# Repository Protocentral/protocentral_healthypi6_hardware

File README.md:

<div align="center">

<picture>
  <source media="(prefers-color-scheme: dark)" srcset="docs/images/healthypi6-logo-dark.png">
  
</picture>

</div>

# HealthyPi 6 — Hardware

Open hardware design files for HealthyPi 6, a standalone vital-signs monitor with a
modular expansion bus.

The device is built around a tri-core architecture — an STM32H757BI (Cortex-M7 +
Cortex-M4) with an ESP32-C6 for wireless — with a 4" capacitive touchscreen, an isolated
supply, an isolated USB port, and two HealthyLink expansion slots that accept new sensing
front-ends without a board respin.

This repository holds the KiCad schematics and PCB layouts, the HealthyLink interface
definition, the enclosure CAD, and the CE/UKCA declarations of conformity.

## Links

| | |
|---|---|
| Product page | https://www.crowdsupply.com/protocentral/healthypi-6 |
| Firmware (Zephyr) | https://github.com/Protocentral/healthypi-6-fw |
| HealthyPi Studio | https://github.com/Protocentral/healthypi_studio |

## Boards

Design files are published as each board is finalised.

| Board | Revision | Role |
|---|---|---|
| [`healthypi_6_main_v5`](hardware/healthypi_6_main_v5/) | **v5** | STM32H757BI main board — AFEs, power, wireless, both HealthyLink slots |
| [`healthypi_6_display_v7`](hardware/healthypi_6_display_v7/) | **v7** | Display interface board — MIPI-DSI and touch to the panel, backlight driver |
| [`healthylink_compute_v5`](hardware/healthylink_compute_v5/) | **v5** | HealthyLink compute / NPU module — STM32N657, camera, storage |
| [`healthylink_gpio_v2`](hardware/healthylink_gpio_v2/) | **v2** | HealthyLink GPIO breakout — the minimal module example |

## Specifications

Cross-checked against the v5 schematic in this repository.

- **Application processor:** STM32H757BI (LQFP208) — Arm Cortex-M7 @ 400 MHz +
  Cortex-M4 @ 200 MHz
- **Wireless:** ESP32-C6-MINI-1 (Wi-Fi 6 / BLE / 802.15.4), UART and SPI to the host MCU,
  plus its own USB-C for direct flashing
- **Display:** 4" 480×800 capacitive touchscreen — 2-lane MIPI-DSI, touch on I²C,
  TPS61158 backlight boost on the display board
- **Biosignal front-ends:** TI ADS1294R (ECG + thoracic respiration), TI AFE4400 (PPG),
  Bosch BMI323 (motion)
- **Expansion:** 2 × HealthyLink slots, 2 × Hirose DF9-31P-1V per slot (62 pins/slot),
  per-slot NCP380 current-limited load switch with fault reporting
- **Power:** isolated 10 W supply (Traco THM 10-0511); TI BQ24074 linear battery charger,
  Maxim MAX17048 fuel gauge, TPS62A02 system buck
- **Memory and storage:** 32 MB SDRAM (Winbond W9825G6KH), 64 MB QSPI NOR
  (Winbond W25Q512JV), microSD
- **Host interface:** USB-C, USB 2.0 full-speed, galvanically isolated through a
  TI ISOUSB111
- **Main board:** 120 × 70 mm, 6-layer

## HealthyLink expansion bus

HealthyLink is the modular expansion system for HealthyPi 6. Each slot presents 62 pins
across two Hirose DF9-31 board-to-board connectors, carrying two SPI buses, I²C, a UART,
six analog inputs, CAN, per-slot interrupt and reset, and a switched 3V3 module rail. The
main board has two slots (A and B).

Modules are **not hot-swappable** — install them with the device powered off.

The full pin assignment and electrical definition is in
[`docs/HEALTHYLINK.md`](docs/HEALTHYLINK.md). The KiCad symbol for the connector is
[`hardware/healthylink_df9_connector.kicad_sym`](hardware/healthylink_df9_connector.kicad_sym) —
use it as the starting point for your own module.

## Enclosure

[`enclosure/`](enclosure/) holds the CAD for the case, in three forms: the editable
Fusion archive, a neutral STEP export per part, and a print-ready STL per part.

| Part | Size |
|---|---|
| `top` | 125 × 75 × 23 mm |
| `bottom` | 125 × 75 × 14 mm |
| `back-cover-with-slots` | 125 × 75 × 3 mm |
| `back-cover-no-slots` | 125 × 75 × 7.5 mm |
| `battery-holder` | 53 × 35 × 14 mm |
| `push-switch` | 8 × 5 × 4 mm |
| `slide-switch` | 7 × 13 × 5 mm |

Every part appears under the same name in both
[`enclosure/step/`](enclosure/step/) and [`enclosure/stl/`](enclosure/stl/). The Fusion
source is [`enclosure/source/healthypi6-enclosure-v5.f3z`](enclosure/source/); open it if
you want to change the geometry rather than print it as-is. The enclosure is drawn around
the 120 × 70 mm main board, so any board modification that moves a connector or a mounting
hole needs a matching change here.

## Repository layout

| Path | Contents |
|---|---|
| [`hardware/`](hardware/) | One folder per board: KiCad project (schematic + PCB) and exported schematic PDF |
| [`docs/`](docs/) | HealthyLink interface definition and images |
| [`enclosure/`](enclosure/) | Enclosure CAD — Fusion source, STEP and STL per part |
| [`compliance/`](compliance/) | CE and UKCA declarations of conformity, safety insert |

## Working from these files

- For firmware, start at the firmware repository. This repo is the electrical reference:
  pin assignments, AFE wiring, connector pinouts.
- To build a HealthyLink module, read [`docs/HEALTHYLINK.md`](docs/HEALTHYLINK.md) and
  copy [`healthylink_gpio_v2`](hardware/healthylink_gpio_v2/), which is the minimal
  working example.
- To respin a board: both projects are saved in **KiCad 10** format and will not open in
  earlier versions. Footprints are embedded in the board files and symbols are cached in
  the schematics, so the projects open standalone. A handful of 3D models resolve through
  an internal `${PROTOCENTRAL}` path and will show as missing in the 3D viewer; this
  affects rendering only, never the netlist or the layout.

## Important notice

This device is intended for **research, education, and evaluation use only**. It is **not**
a medical diagnostic instrument, and it is not FDA-approved or otherwise cleared for
clinical or consumer diagnostic use. The CE and UKCA declarations in
[`compliance/`](compliance/) cover EMC and electrical safety for the device as an
electronic product — they are not medical device certifications.

Do not use HealthyPi 6 to make medical decisions.

## License

The hardware design files in this repository are licensed under the **CERN Open Hardware
Licence Version 2 – Permissive (CERN-OHL-P v2)**. See [LICENSE](LICENSE).

Firmware and software for HealthyPi 6 are licensed separately under the MIT License in
their own repositories.

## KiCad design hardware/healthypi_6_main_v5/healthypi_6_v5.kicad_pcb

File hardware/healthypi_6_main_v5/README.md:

# HealthyPi 6 Main Board

| | |
|---|---|
| Revision | **v5** |
| Role | STM32H757BI host, AFEs, power, wireless, 2 × HealthyLink slots |
| Board | 120 × 70 mm, 6-layer |
| KiCad | 10 |
| Schematic PDF | [`healthypi6-main-v5-schematic.pdf`](healthypi6-main-v5-schematic.pdf) |

## Files

| File | Contents |
|---|---|
| `healthypi_6_v5.kicad_pro` / `.kicad_sch` / `.kicad_pcb` | KiCad project for this revision |
| `healthypi6-main-v5-schematic.pdf` | Exported schematic — the human-readable reference |

## Schematic sheets

| Sheet | File | Contents |
|---|---|---|
| MCU | `mcu.kicad_sch` | STM32H757BI, clocks, SWD, buttons, buzzer |
| ECG Frontend | `ecg_afe.kicad_sch` | TI ADS1294R, ECG input protection |
| PPG Frontend | `ppg_sensor.kicad_sch` | TI AFE4400, Bosch BMI323, DE9 patient connector |
| Memory | `memory.kicad_sch` | SDRAM, QSPI NOR, microSD |
| USB | `io.kicad_sch` | USB-C, ISOUSB111 isolator, isolated 10 W supply |
| Power | `power.kicad_sch` | Battery charger, fuel gauge, system rails |
| Power 2 | `power2.kicad_sch` | Per-slot HealthyLink load switches |
| Wireless | `wireless.kicad_sch` | ESP32-C6-MINI-1 and its USB-C |
| connectors | `connectors.kicad_sch` | Display FFC, front-panel and auxiliary connectors |
| healthylink | `healthylink.kicad_sch` | Both HealthyLink slots — see [`docs/HEALTHYLINK.md`](../../docs/HEALTHYLINK.md) |

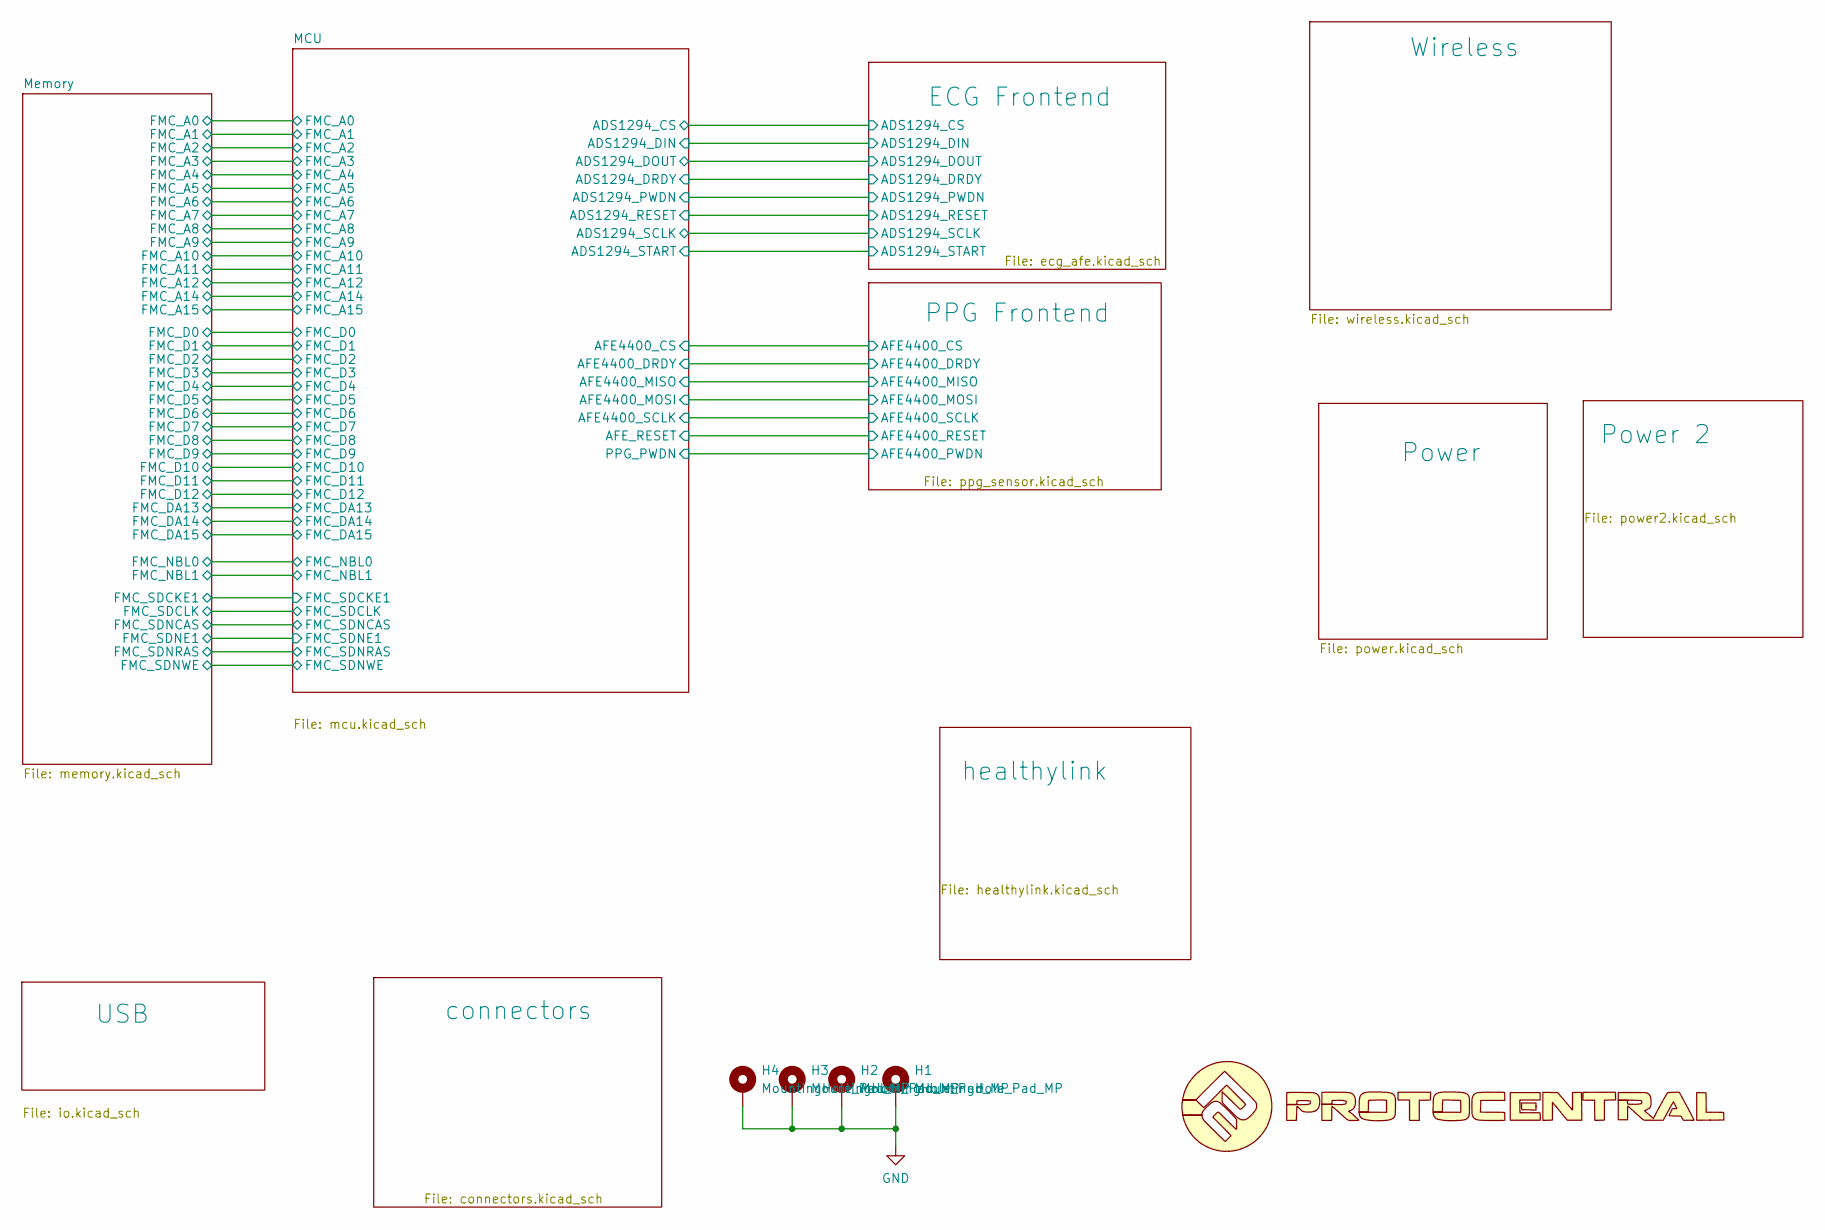
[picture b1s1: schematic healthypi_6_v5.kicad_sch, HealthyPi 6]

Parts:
H1, H2, H3, H4: MountingHole_Pad_MP; MountingHole_3.2mm_M3_DIN965_Pad_TopBottom
U4: LOGO

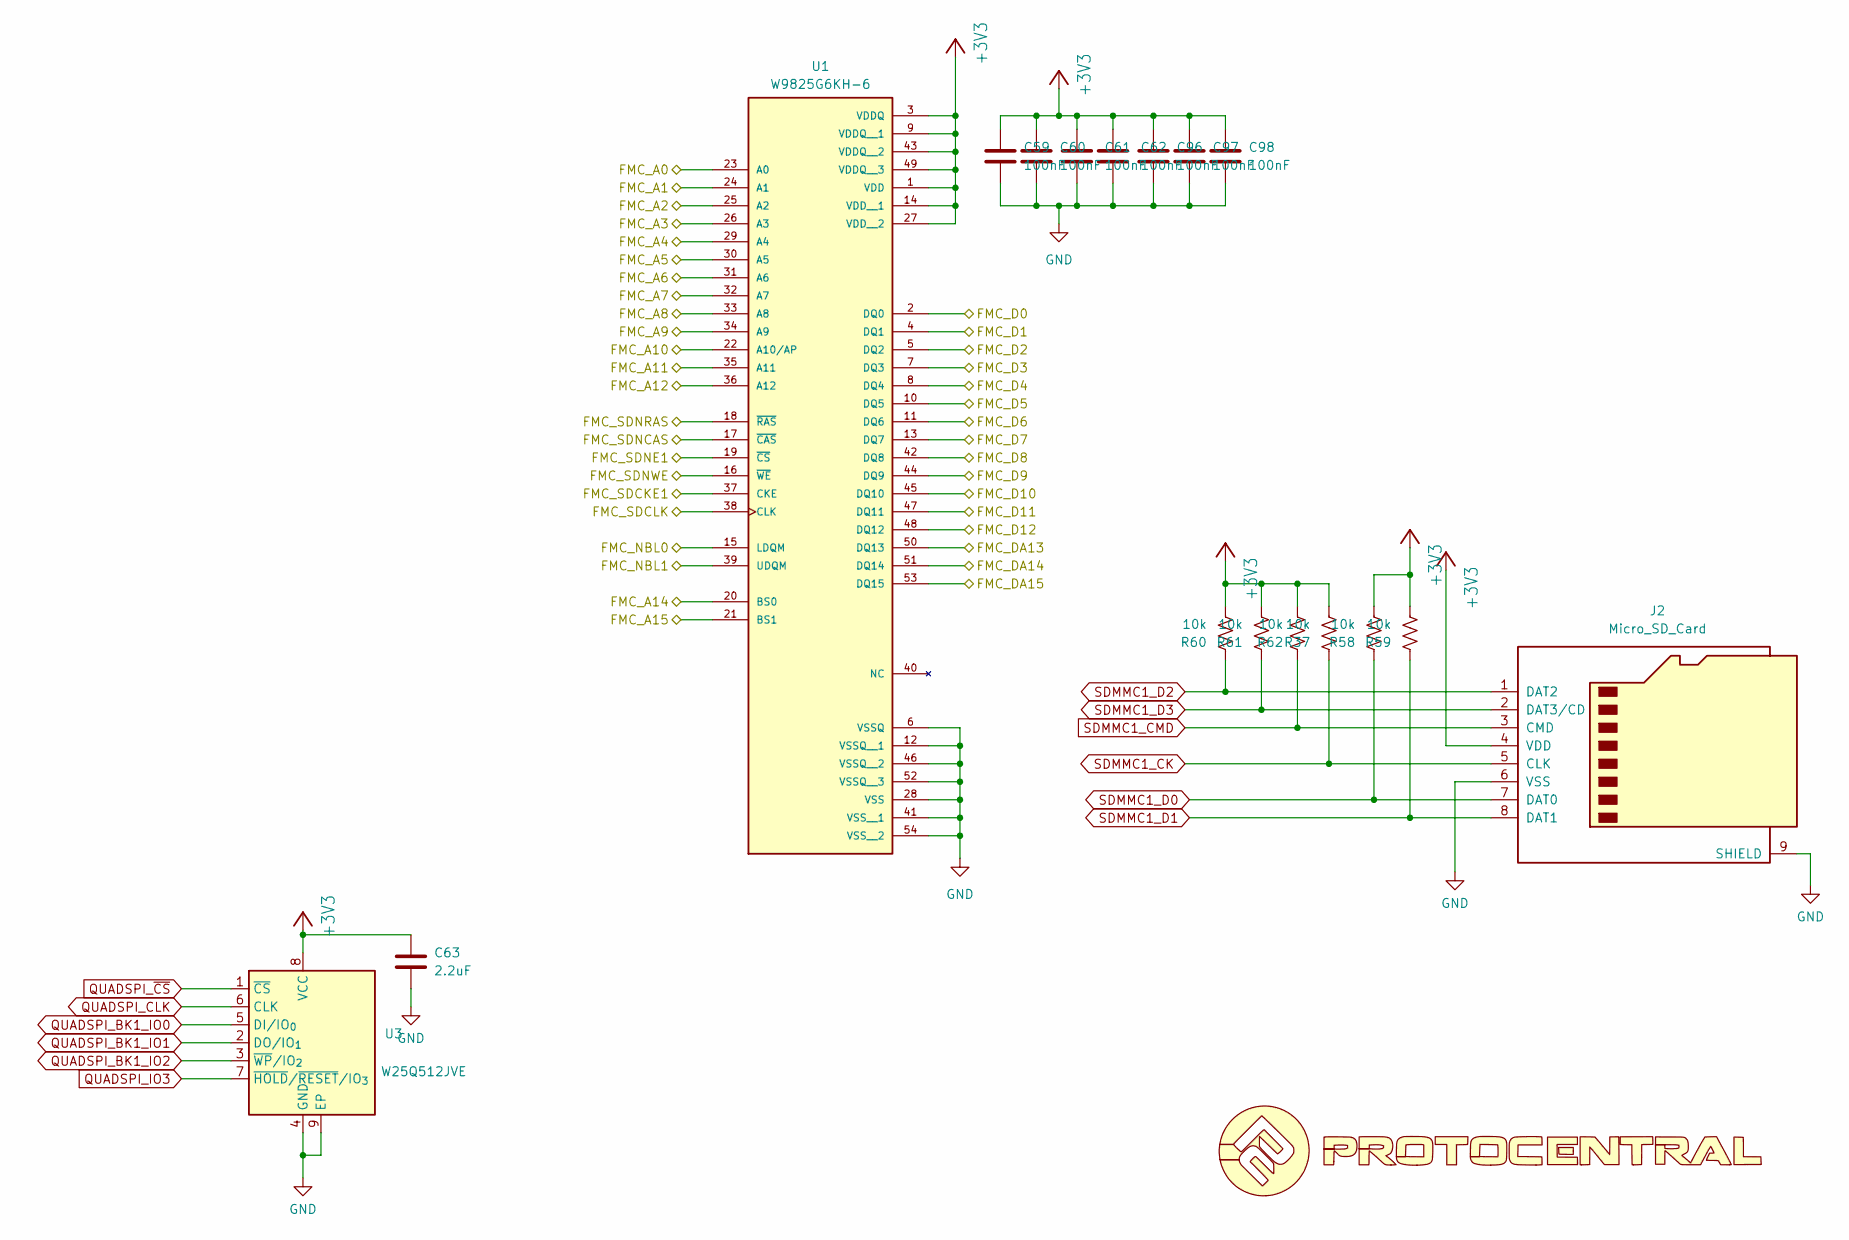
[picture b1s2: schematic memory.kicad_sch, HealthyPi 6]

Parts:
C59, C60, C61, C62, C96, C97, C98: 100nF; C_0402_1005Metric
C63: 2.2uF; C_0402_1005Metric
J2: Micro_SD_Card; GCT_MEM2052-00-195-00-A_REVA
R37, R58, R59, R60, R61, R62: 10k; R_0402_1005Metric
U1: W9825G6KH-6; SOP80P1176X120-54N; PARTREV A05
U3: W25Q512JVE; WSON-8-1EP_8x6mm_P1.27mm_EP3.4x4.3mm
U16: LOGO

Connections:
+3V3: C59.2, C60.2, C61.2, C62.2, C63.2, C96.2, C97.2, C98.2, J2.4 (VDD), R37.2, R58.2, R59.2, R60.2, R61.2, R62.2, U1.1 (VDD), U1.3 (VDDQ), U1.9 (VDDQ__1), U1.14 (VDD__1), U1.27 (VDD__2), U1.43 (VDDQ__2), U1.49 (VDDQ__3), U3.8 (VCC); also elsewhere on the board
/MCU/FMC_A0: U1.23 (A0); also elsewhere on the board
/MCU/FMC_A1: U1.24 (A1); also elsewhere on the board
/MCU/FMC_A2: U1.25 (A2); also elsewhere on the board
/MCU/FMC_A3: U1.26 (A3); also elsewhere on the board
/MCU/FMC_A4: U1.29 (A4); also elsewhere on the board
/MCU/FMC_A5: U1.30 (A5); also elsewhere on the board
/MCU/FMC_A6: U1.31 (A6); also elsewhere on the board
/MCU/FMC_A7: U1.32 (A7); also elsewhere on the board
/MCU/FMC_A8: U1.33 (A8); also elsewhere on the board
/MCU/FMC_A9: U1.34 (A9); also elsewhere on the board
/MCU/FMC_A10: U1.22 (A10/AP); also elsewhere on the board
/MCU/FMC_A11: U1.35 (A11); also elsewhere on the board
/MCU/FMC_A12: U1.36 (A12); also elsewhere on the board
/MCU/FMC_A14: U1.20 (BS0); also elsewhere on the board
/MCU/FMC_A15: U1.21 (BS1); also elsewhere on the board
/MCU/FMC_D0: U1.2 (DQ0); also elsewhere on the board
/MCU/FMC_D1: U1.4 (DQ1); also elsewhere on the board
/MCU/FMC_D2: U1.5 (DQ2); also elsewhere on the board
/MCU/FMC_D3: U1.7 (DQ3); also elsewhere on the board
/MCU/FMC_D4: U1.8 (DQ4); also elsewhere on the board
/MCU/FMC_D5: U1.10 (DQ5); also elsewhere on the board
/MCU/FMC_D6: U1.11 (DQ6); also elsewhere on the board
/MCU/FMC_D7: U1.13 (DQ7); also elsewhere on the board
/MCU/FMC_D8: U1.42 (DQ8); also elsewhere on the board
/MCU/FMC_D9: U1.44 (DQ9); also elsewhere on the board
/MCU/FMC_D10: U1.45 (DQ10); also elsewhere on the board
/MCU/FMC_D11: U1.47 (DQ11); also elsewhere on the board
/MCU/FMC_D12: U1.48 (DQ12); also elsewhere on the board
/MCU/FMC_DA13: U1.50 (DQ13); also elsewhere on the board
/MCU/FMC_DA14: U1.51 (DQ14); also elsewhere on the board
/MCU/FMC_DA15: U1.53 (DQ15); also elsewhere on the board
/MCU/FMC_NBL0: U1.15 (LDQM); also elsewhere on the board
/MCU/FMC_NBL1: U1.39 (UDQM); also elsewhere on the board
/MCU/FMC_SDCKE1: U1.37 (CKE); also elsewhere on the board
/MCU/FMC_SDCLK: U1.38 (CLK); also elsewhere on the board
/MCU/FMC_SDNCAS: U1.17 (~CAS); also elsewhere on the board
/MCU/FMC_SDNE1: U1.19 (~CS); also elsewhere on the board
/MCU/FMC_SDNRAS: U1.18 (~RAS); also elsewhere on the board
/MCU/FMC_SDNWE: U1.16 (~WE); also elsewhere on the board
GND: C59.1, C60.1, C61.1, C62.1, C63.1, C96.1, C97.1, C98.1, J2.6 (VSS), J2.9 (SHIELD), U1.6 (VSSQ), U1.12 (VSSQ__1), U1.28 (VSS), U1.41 (VSS__1), U1.46 (VSSQ__2), U1.52 (VSSQ__3), U1.54 (VSS__2), U3.4 (GND), U3.9 (EP); also elsewhere on the board
QUADSPI_BK1_IO0: U3.5 (DI/IO_{0}); also elsewhere on the board
QUADSPI_BK1_IO1: U3.2 (DO/IO_{1}); also elsewhere on the board
QUADSPI_BK1_IO2: U3.3 (~WP/IO_{2}); also elsewhere on the board
QUADSPI_CLK: U3.6 (CLK); also elsewhere on the board
QUADSPI_IO3: U3.7 (~HOLD/~RESET/IO_{3}); also elsewhere on the board
QUADSPI_~CS: U3.1 (~CS); also elsewhere on the board
SDMMC1_CK: J2.5 (CLK), R37.1; also elsewhere on the board
SDMMC1_CMD: J2.3 (CMD), R62.1; also elsewhere on the board
SDMMC1_D0: J2.7 (DAT0), R58.1; also elsewhere on the board
SDMMC1_D1: J2.8 (DAT1), R59.1; also elsewhere on the board
SDMMC1_D2: J2.1 (DAT2), R60.1; also elsewhere on the board
SDMMC1_D3: J2.2 (DAT3/CD), R61.1; also elsewhere on the board

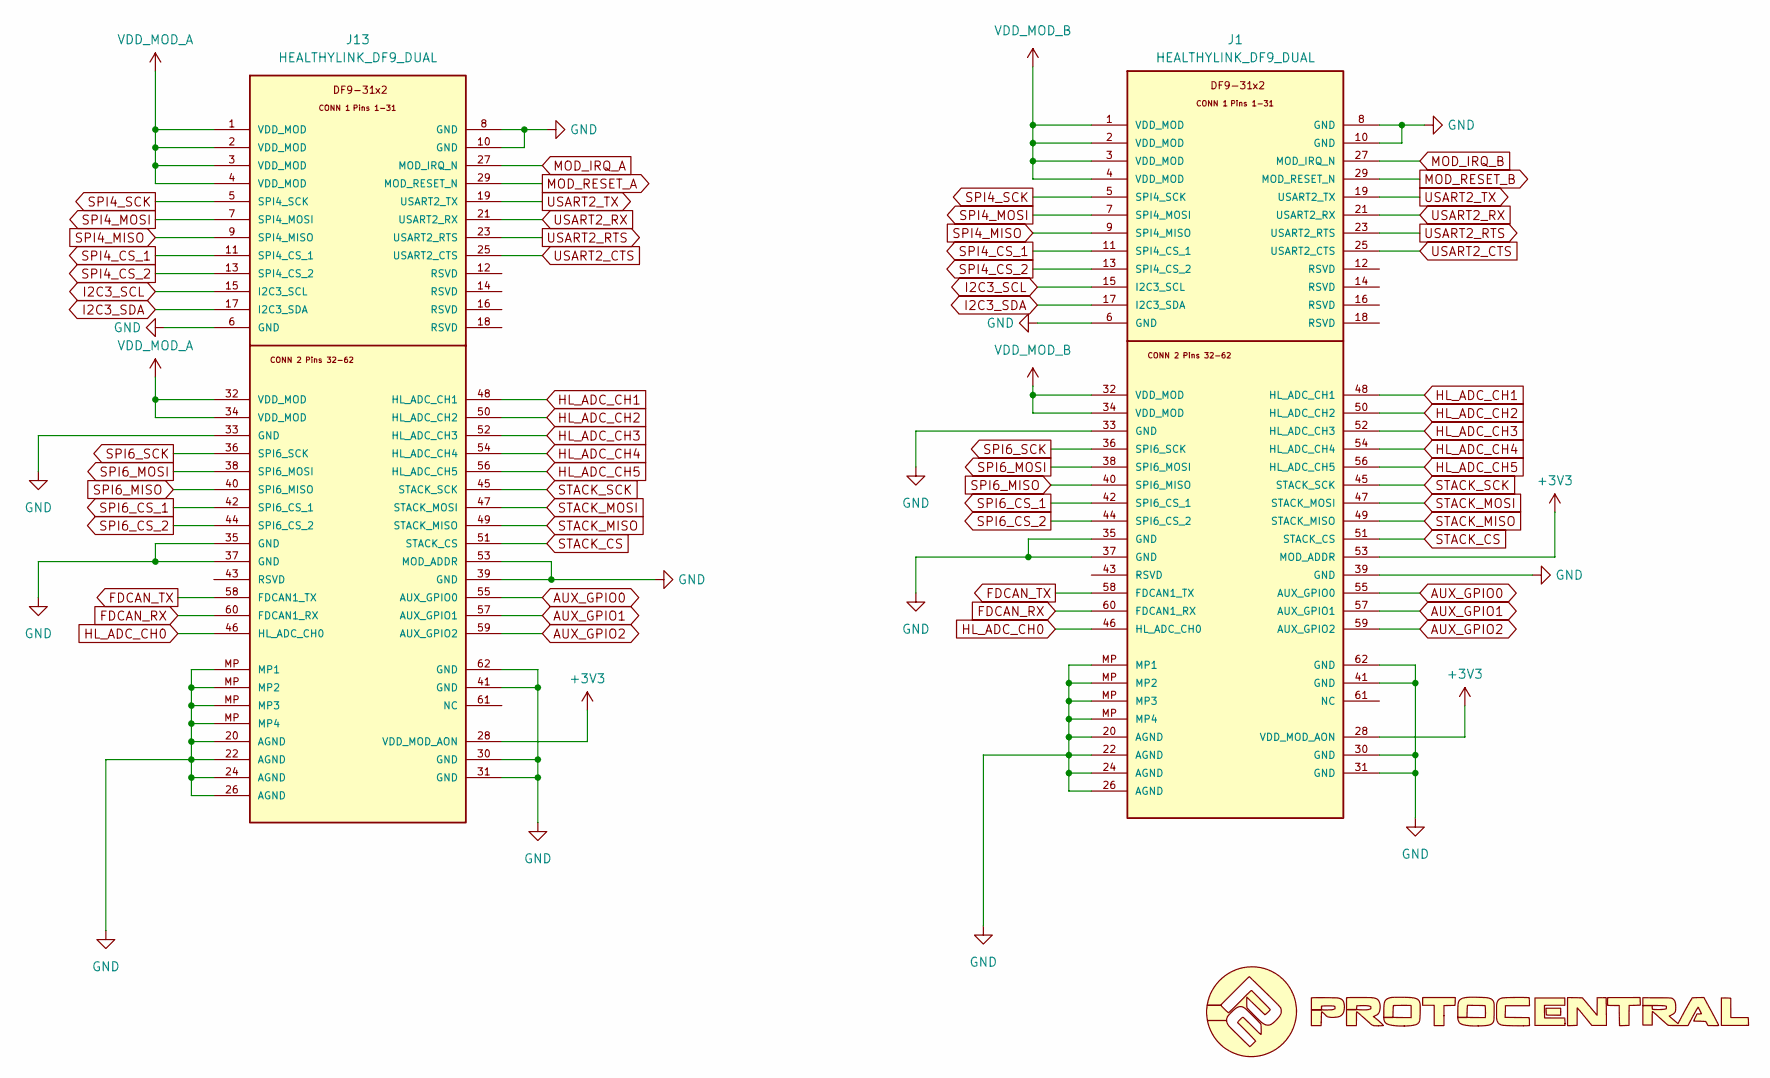
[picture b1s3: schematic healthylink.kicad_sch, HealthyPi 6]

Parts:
J1, J13: HEALTHYLINK_DF9_DUAL; healthylink_df9_module_slot
U23: LOGO

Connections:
+3V3: J1.28 (VDD_MOD_AON), J1.53 (MOD_ADDR), J13.28 (VDD_MOD_AON); also elsewhere on the board
AUX_GPIO0: J1.55 (AUX_GPIO0), J13.55 (AUX_GPIO0); also elsewhere on the board
AUX_GPIO1: J1.57 (AUX_GPIO1), J13.57 (AUX_GPIO1); also elsewhere on the board
AUX_GPIO2: J1.59 (AUX_GPIO2), J13.59 (AUX_GPIO2); also elsewhere on the board
FDCAN_RX: J1.60 (FDCAN1_RX), J13.60 (FDCAN1_RX); also elsewhere on the board
FDCAN_TX: J1.58 (FDCAN1_TX), J13.58 (FDCAN1_TX); also elsewhere on the board
GND: J1.6 (GND), J1.8 (GND), J1.10 (GND), J1.20 (AGND), J1.22 (AGND), J1.24 (AGND), J1.26 (AGND), J1.30 (GND), J1.31 (GND), J1.33 (GND), J1.35 (GND), J1.37 (GND), J1.39 (GND), J1.41 (GND), J1.62 (GND), J1.MP (MP4), J13.6 (GND), J13.8 (GND), J13.10 (GND), J13.20 (AGND), J13.22 (AGND), J13.24 (AGND), J13.26 (AGND), J13.30 (GND), J13.31 (GND), J13.33 (GND), J13.35 (GND), J13.37 (GND), J13.39 (GND), J13.41 (GND), J13.53 (MOD_ADDR), J13.62 (GND), J13.MP (MP1); also elsewhere on the board
HL_ADC_CH0: J1.46 (HL_ADC_CH0), J13.46 (HL_ADC_CH0); also elsewhere on the board
HL_ADC_CH1: J1.48 (HL_ADC_CH1), J13.48 (HL_ADC_CH1); also elsewhere on the board
HL_ADC_CH2: J1.50 (HL_ADC_CH2), J13.50 (HL_ADC_CH2); also elsewhere on the board
HL_ADC_CH3: J1.52 (HL_ADC_CH3), J13.52 (HL_ADC_CH3); also elsewhere on the board
HL_ADC_CH4: J1.54 (HL_ADC_CH4), J13.54 (HL_ADC_CH4); also elsewhere on the board
HL_ADC_CH5: J1.56 (HL_ADC_CH5), J13.56 (HL_ADC_CH5); also elsewhere on the board
I2C3_SCL: J1.15 (I2C3_SCL), J13.15 (I2C3_SCL); also elsewhere on the board
I2C3_SDA: J1.17 (I2C3_SDA), J13.17 (I2C3_SDA); also elsewhere on the board
MOD_IRQ_A: J13.27 (MOD_IRQ_N); also elsewhere on the board
MOD_IRQ_B: J1.27 (MOD_IRQ_N); also elsewhere on the board
MOD_RESET_A: J13.29 (MOD_RESET_N); also elsewhere on the board
MOD_RESET_B: J1.29 (MOD_RESET_N); also elsewhere on the board
SPI4_CS_1: J1.11 (SPI4_CS_1), J13.11 (SPI4_CS_1); also elsewhere on the board
SPI4_CS_2: J1.13 (SPI4_CS_2), J13.13 (SPI4_CS_2); also elsewhere on the board
SPI4_MISO: J1.9 (SPI4_MISO), J13.9 (SPI4_MISO); also elsewhere on the board
SPI4_MOSI: J1.7 (SPI4_MOSI), J13.7 (SPI4_MOSI); also elsewhere on the board
SPI4_SCK: J1.5 (SPI4_SCK), J13.5 (SPI4_SCK); also elsewhere on the board
SPI6_CS_1: J1.42 (SPI6_CS_1), J13.42 (SPI6_CS_1); also elsewhere on the board
SPI6_CS_2: J1.44 (SPI6_CS_2), J13.44 (SPI6_CS_2); also elsewhere on the board
SPI6_MISO: J1.40 (SPI6_MISO), J13.40 (SPI6_MISO); also elsewhere on the board
SPI6_MOSI: J1.38 (SPI6_MOSI), J13.38 (SPI6_MOSI); also elsewhere on the board
SPI6_SCK: J1.36 (SPI6_SCK), J13.36 (SPI6_SCK); also elsewhere on the board
STACK_CS: J1.51 (STACK_CS), J13.51 (STACK_CS)
STACK_MISO: J1.49 (STACK_MISO), J13.49 (STACK_MISO)
STACK_MOSI: J1.47 (STACK_MOSI), J13.47 (STACK_MOSI)
STACK_SCK: J1.45 (STACK_SCK), J13.45 (STACK_SCK)
USART2_CTS: J1.25 (USART2_CTS), J13.25 (USART2_CTS); also elsewhere on the board
USART2_RTS: J1.23 (USART2_RTS), J13.23 (USART2_RTS); also elsewhere on the board
USART2_RX: J1.21 (USART2_RX), J13.21 (USART2_RX); also elsewhere on the board
USART2_TX: J1.19 (USART2_TX), J13.19 (USART2_TX); also elsewhere on the board
VDD_MOD_A: J13.1 (VDD_MOD), J13.2 (VDD_MOD), J13.3 (VDD_MOD), J13.4 (VDD_MOD), J13.32 (VDD_MOD), J13.34 (VDD_MOD); also elsewhere on the board
VDD_MOD_B: J1.1 (VDD_MOD), J1.2 (VDD_MOD), J1.3 (VDD_MOD), J1.4 (VDD_MOD), J1.32 (VDD_MOD), J1.34 (VDD_MOD); also elsewhere on the board

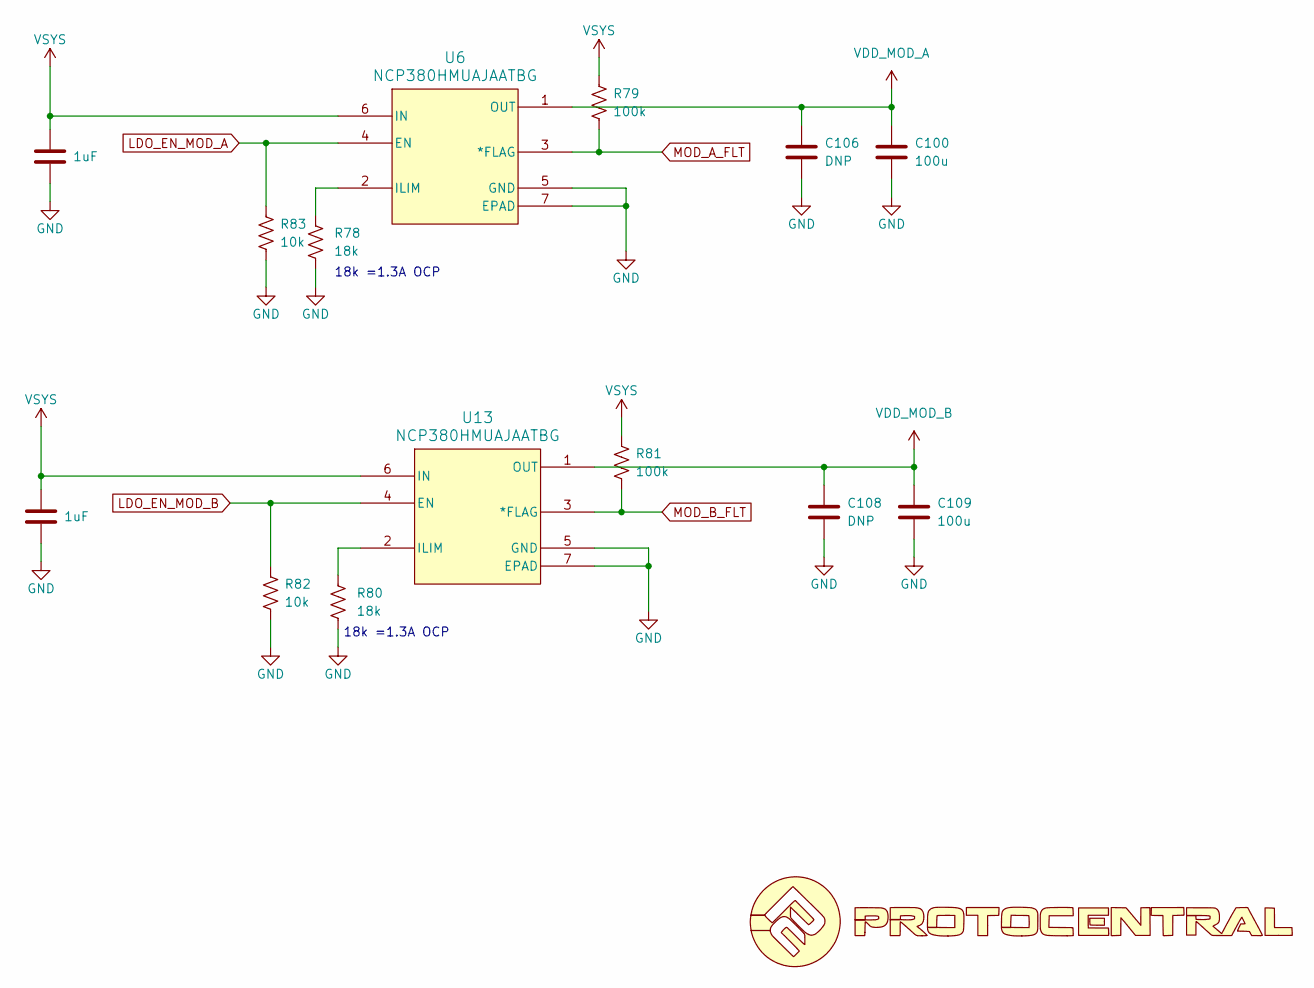
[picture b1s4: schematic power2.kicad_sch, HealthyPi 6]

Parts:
C75, C107: 1uF; C_0402_1005Metric; Voltage 10V; Tolerance 20%
C100, C109: 100u; C_1206_3216Metric
C106, C108: DNP; C_0805_2012Metric
R78, R80: 18k; R_0402_1005Metric
R79, R81: 100k; R_0402_1005Metric
R82, R83: 10k; R_0402_1005Metric
U6, U13: NCP380HMUAJAATBG; UDFN6_2X2_ONS
U24: LOGO

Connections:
GND: C75.2, C100.2, C106.2, C107.2, C108.2, C109.2, R78.1, R80.1, R82.1, R83.1, U6.5 (GND), U6.7 (EPAD), U13.5 (GND), U13.7 (EPAD); also elsewhere on the board
LDO_EN_MOD_A: R83.2, U6.4 (EN); also elsewhere on the board
LDO_EN_MOD_B: R82.2, U13.4 (EN); also elsewhere on the board
MOD_A_FLT: R79.1, U6.3 (*FLAG); also elsewhere on the board
MOD_B_FLT: R81.1, U13.3 (*FLAG); also elsewhere on the board
unnamed: R78.2, U6.2 (ILIM)
unnamed: R80.2, U13.2 (ILIM)
VDD_MOD_A: C100.1, C106.1, U6.1 (OUT); also elsewhere on the board
VDD_MOD_B: C108.1, C109.1, U13.1 (OUT); also elsewhere on the board
VSYS: C75.1, C107.1, R79.2, R81.2, U6.6 (IN), U13.6 (IN); also elsewhere on the board

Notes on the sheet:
18k =1.3A OCP

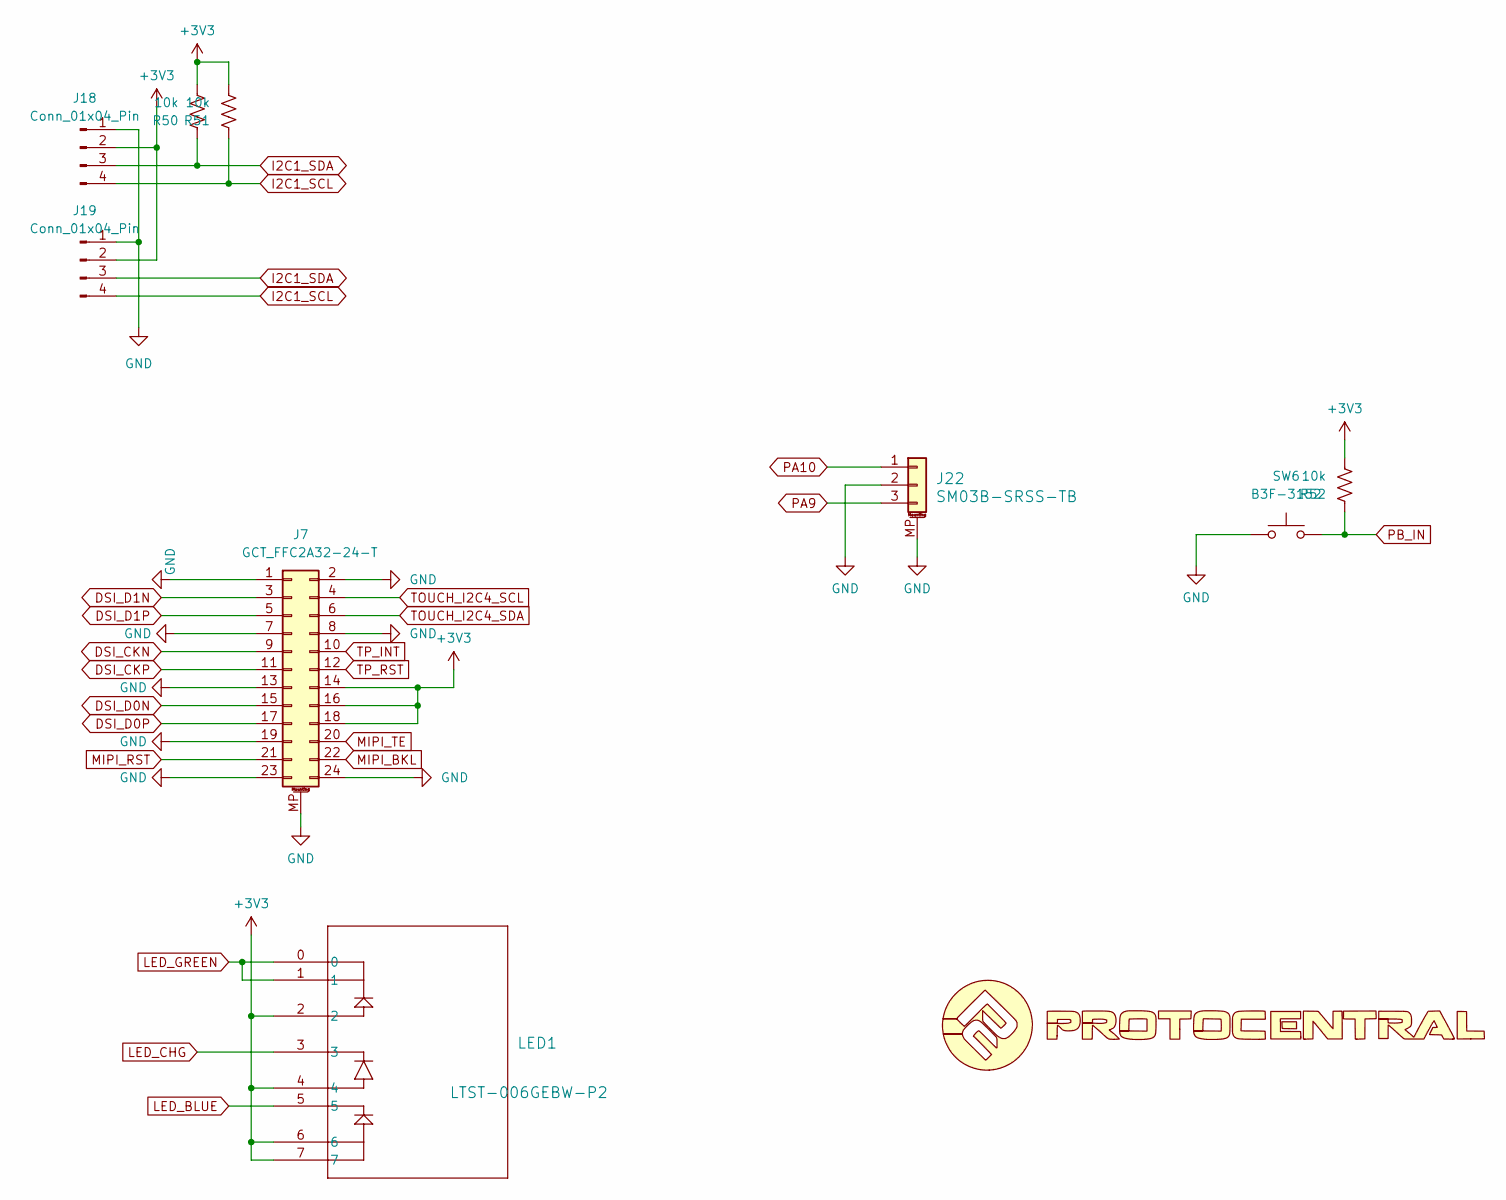
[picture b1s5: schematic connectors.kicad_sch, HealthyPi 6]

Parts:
J7: GCT_FFC2A32-24-T
J18, J19: Conn_01x04_Pin; JST_SH_SM04B-SRSS-TB_1x04-1MP_P1.00mm_Horizontal
J22: SM03B-SRSS-TB; JST_SH_SM03B-SRSS-TB_1x03-1MP_P1.00mm_Horizontal
LED1: LTST-006GEBW-P2; LTST-008BGEW_LTO
R50, R51, R52: 10k; R_0402_1005Metric
SW6: B3F-3152; SW_SPST_Omron_B3F-315x_Angled
U22: LOGO

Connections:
+3V3: J7.14, J7.16, J7.18, J18.2, J19.2, LED1.2, LED1.4, LED1.6, LED1.7, R50.2, R51.2, R52.2; also elsewhere on the board
DSI_CKN: J7.9; also elsewhere on the board
DSI_CKP: J7.11; also elsewhere on the board
DSI_D0N: J7.15; also elsewhere on the board
DSI_D0P: J7.17; also elsewhere on the board
DSI_D1N: J7.3; also elsewhere on the board
DSI_D1P: J7.5; also elsewhere on the board
GND: J7.1, J7.2, J7.7, J7.8, J7.13, J7.19, J7.23, J7.24, J7.MP (MountPin), J18.1, J19.1, J22.2, J22.MP (MountPin), SW6.1; also elsewhere on the board
I2C1_SCL: J18.4, J19.4, R51.1; also elsewhere on the board
I2C1_SDA: J18.3, J19.3, R50.1; also elsewhere on the board
LED_BLUE: LED1.5; also elsewhere on the board
LED_CHG: LED1.3; also elsewhere on the board
LED_GREEN: LED1.0, LED1.1; also elsewhere on the board
MIPI_BKL: J7.22; also elsewhere on the board
MIPI_RST: J7.21; also elsewhere on the board
MIPI_TE: J7.20; also elsewhere on the board
PA9: J22.3; also elsewhere on the board
PA10: J22.1; also elsewhere on the board
PB_IN: R52.1, SW6.2; also elsewhere on the board
TOUCH_I2C4_SCL: J7.4; also elsewhere on the board
TOUCH_I2C4_SDA: J7.6; also elsewhere on the board
TP_INT: J7.10; also elsewhere on the board
TP_RST: J7.12; also elsewhere on the board
